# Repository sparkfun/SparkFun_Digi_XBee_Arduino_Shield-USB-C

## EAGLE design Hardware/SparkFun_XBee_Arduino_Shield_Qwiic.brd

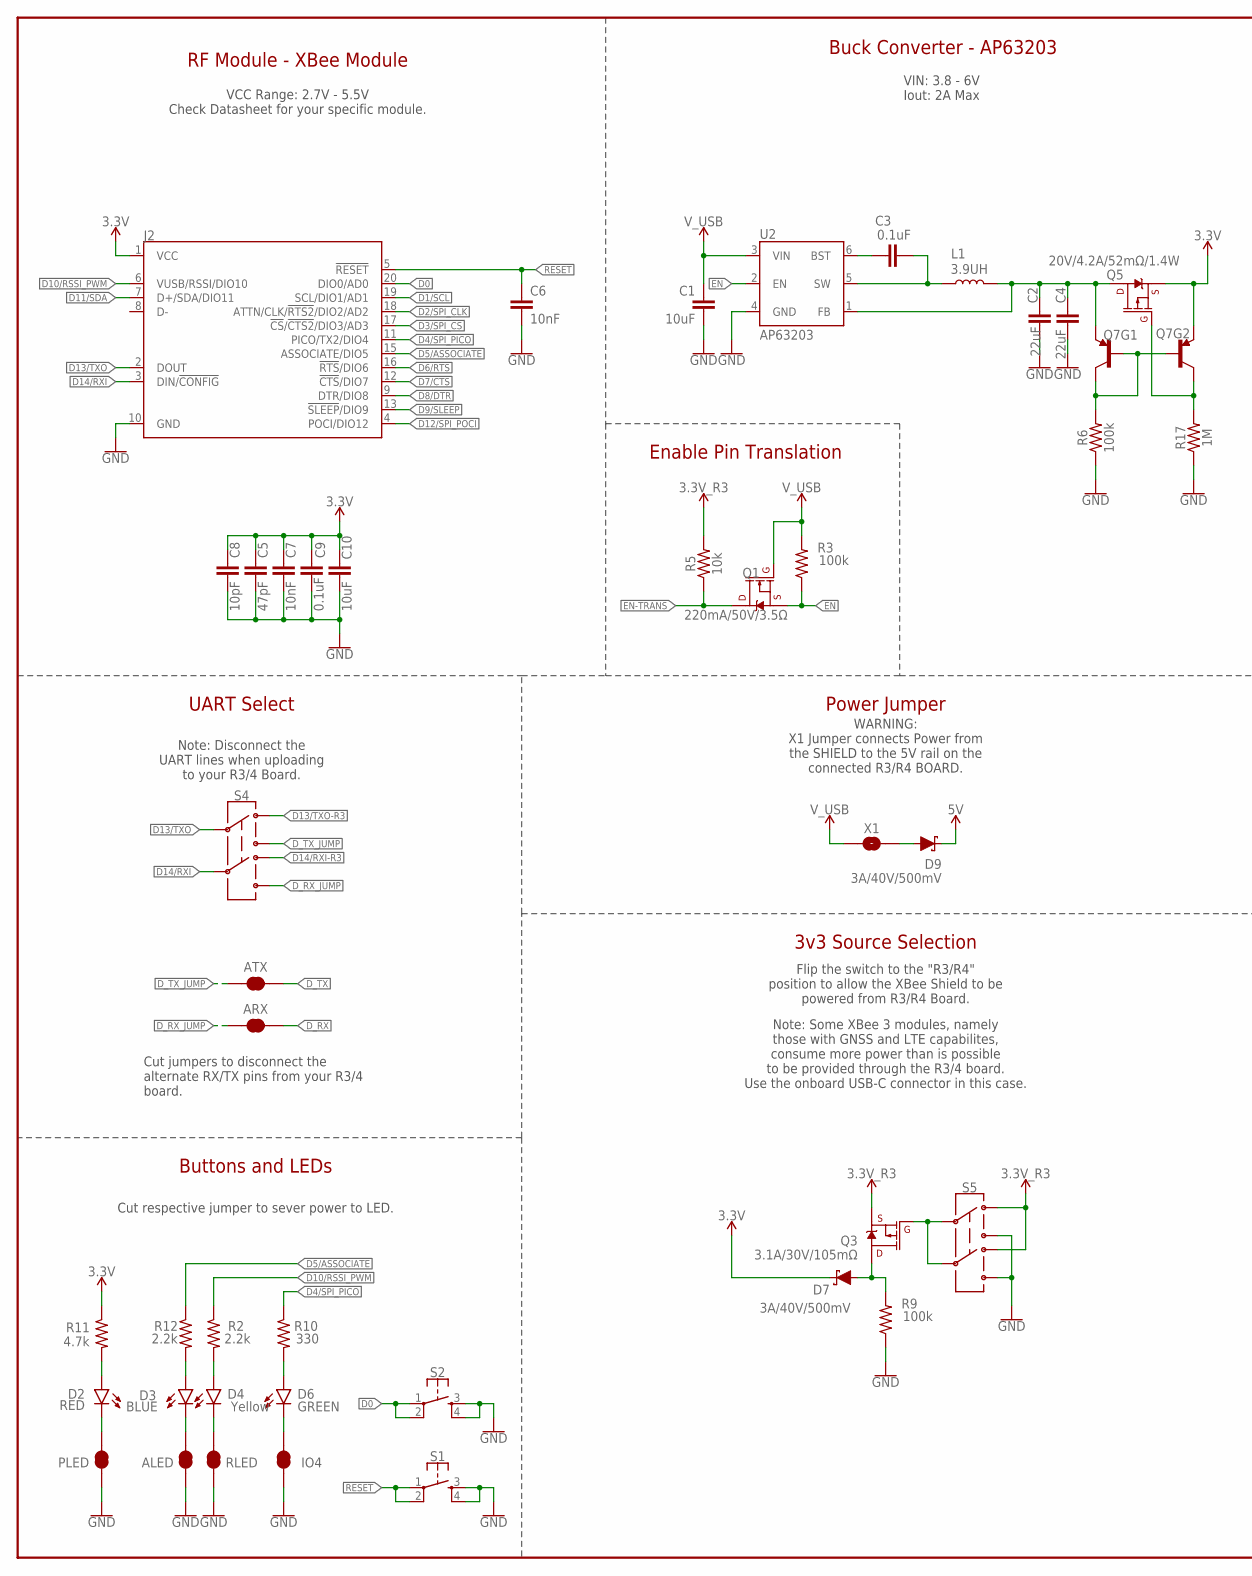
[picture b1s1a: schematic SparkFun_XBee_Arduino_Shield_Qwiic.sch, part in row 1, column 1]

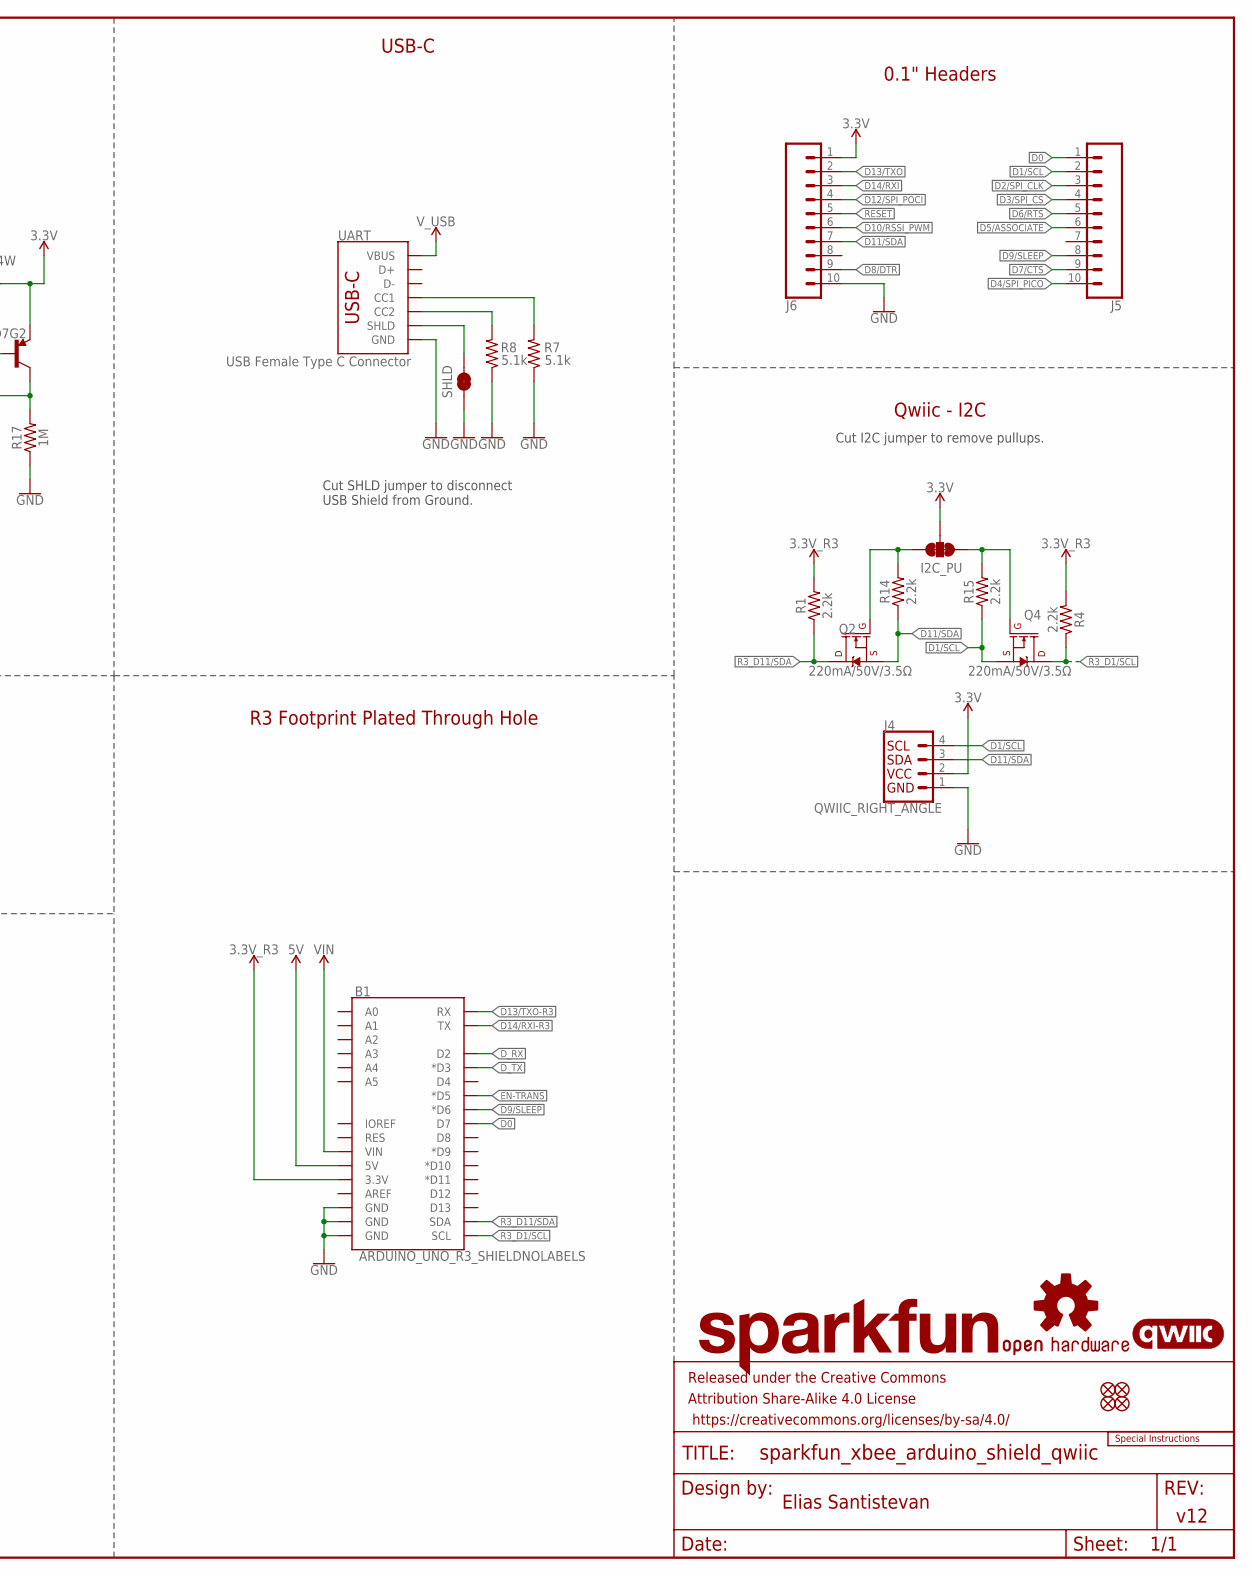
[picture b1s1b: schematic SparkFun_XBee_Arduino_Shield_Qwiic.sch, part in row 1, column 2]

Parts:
ALED: JUMPER-SMT_2_NC_TRACE_SILK; SMT-JUMPER_2_NC_TRACE_SILK
ARX: JUMPER-SMT_2_NC_TRACE_SILK; SMT-JUMPER_2_NC_TRACE_SILK
ATX: JUMPER-SMT_2_NC_TRACE_SILK; SMT-JUMPER_2_NC_TRACE_SILK
B1: ARDUINO_UNO_R3_SHIELDNOLABELS; UNO_R3_SHIELD_NOLABELS
C1: 10uF; 1210
C2, C4: 22uF; 0603
C3, C9: 0.1uF; 0603
C5: 47pF; 0603
C6, C7: 10nF; 0603
C8: 10pF; 0603
C10: 10uF; 0603
D2: RED; LED-0603
D3: BLUE; LED-0603
D4: Yellow; LED-0603
D6: GREEN; LED-0603
D7, D9: 3A/40V/500mV; SMA-DIODE
FD1, FD2, FD3, FD4: FIDUCIAL1X2; FIDUCIAL-1X2
FRAME1: FRAME-LEDGER; CREATIVE_COMMONS
I2C_PU: JUMPER-SMT_3_2-NC_TRACE_SILK; SMT-JUMPER_3_2-NC_TRACE_SILK
IO4: JUMPER-SMT_2_NC_TRACE_SILK; SMT-JUMPER_2_NC_TRACE_SILK
J2: XBEE_UPDATEXBEE_SMD; XBEE3-SMD
J4: QWIIC_RIGHT_ANGLE; JST04_1MM_RA
J5, J6: CONN_10NO_SILK_PTH_FEMALE; 1X10_NO_SILK
L1: 3.9UH; INDUCTOR_3.9UH
LOGO1: SFE_LOGO_NAMEBLANK; BLANK
LOGO2: OSHW-LOGOS; OSHW-LOGO-S
LOGO3: QWIIC_LOGO_4MM; QWIIC_4MM
LOGO4: SPECIAL_INSTRUCTIONS-ORDERING; ORDERING_INSTRUCTIONS
PLED: JUMPER-SMT_2_NC_TRACE_SILK; SMT-JUMPER_2_NC_TRACE_SILK
Q1, Q2, Q4: 220mA/50V/3.5Ω; SOT23-3
Q3: 3.1A/30V/105mΩ; SOT23-3
Q5: 20V/4.2A/52mΩ/1.4W; SOT23-3
Q7: TRANS_PNP_DUALSOT-363; SOT363_PHILIPS
R1, R2, R4, R12, R14, R15: 2.2k; 0603
R3, R6, R9: 100k; 0603
R5: 10k; 0603
R7, R8: 5.1k; 0603
R10: 330; 0603
R11: 4.7k; 0603
R17: 1M; 0603
RLED: JUMPER-SMT_2_NC_TRACE_SILK; SMT-JUMPER_2_NC_TRACE_SILK
S1, S2: MOMENTARY-SWITCH-SPST-2-SMD-5.2MM-TALL; TACTILE_SWITCH_SMD_5.2MM
S4, S5: SWITCH-DPDT-SMD-AYZ0202; SWITCH_DPDT_SMD_AYZ0202
SHLD: JUMPER-SMT_2_NC_TRACE_SILK; SMT-JUMPER_2_NC_TRACE_SILK
U2: AP63203; SOT23-6
UART: USB Female Type C Connector; USB-C-16P-4LAYER-ISOLATED
X1: JUMPER-SMT_2_NO_SILK; SMT-JUMPER_2_NO_SILK

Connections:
3.3V: C5.1, C7.1, C8.1, C9.1, C10.1, D7.C, I2C_PU.2, J2.1 (VCC), J4.2, J6.1, Q5.2 (S), Q7.4 (E), R11.1
3.3V_R3: B1.3.3V, Q3.2 (S), R1.2, R4.2, R5.2, S5.3, S5.6
3.3V_VREG: C2.1, C4.1, L1.P$2 (2), Q5.3 (D), Q7.1 (E), U2.1 (FB)
5V: B1.5V, D9.C
!RESET!: C6.1, J2.5 (!RESET!), J6.5, S1.1, S1.2
D0: B1.D7, J2.20 (DIO0/AD0), J5.1, S2.1, S2.2
D1/SCL: J2.19 (SCL/DIO1/AD1), J4.4, J5.2, Q4.2 (S), R15.1
D2/SPI_CLK: J2.18 (ATTN/CLK/!RTS2!/DIO2/AD2), J5.3
D3/SPI_!CS!: J2.17 (!CS!/!CTS2!/DIO3/AD3), J5.4
D4/SPI_PICO: J2.11 (PICO/TX2/DIO4), J5.10, R10.1
D5/ASSOCIATE: J2.15 (ASSOCIATE/DIO5), J5.6, R12.1
D6/!RTS!: J2.16 (!RTS!/DIO6), J5.5
D7/!CTS!: J2.12 (!CTS!/DIO7), J5.9
D8/!DTR!: J2.9 (DTR/DIO8), J6.9
D9/!SLEEP!: B1.D6 (*D6), J2.13 (!SLEEP!/DIO9), J5.8
D10/RSSI_PWM: J2.6 (VUSB/RSSI/DIO10), J6.6, R2.1
D11/SDA: J2.7 (D+/SDA/DIO11), J4.3, J6.7, Q2.2 (S), R14.1
D12/SPI_POCI: J2.4 (POCI/DIO12), J6.4
D13/TXO: J2.2 (DOUT), J6.2, S4.2
D13/TXO-R3: B1.RX, S4.3
D14/RXI: J2.3 (DIN/!CONFIG!), J6.3, S4.5
D14/RXI-R3: B1.TX, S4.6
D_RX: ARX.2, B1.D2
D_RX_JUMP: ARX.1, S4.4
D_TX: ATX.2, B1.D3 (*D3)
D_TX_JUMP: ATX.1, S4.1
EN: Q1.2 (S), R3.1, U2.2 (EN)
EN-TRANS: B1.D5 (*D5), Q1.3 (D), R5.1
GND: ALED.1, B1.GND@0 (GND), B1.GND@1 (GND), B1.GND@2 (GND), C1.2, C2.2, C4.2, C5.2, C6.2, C7.2, C8.2, C9.2, C10.2, IO4.1, J2.10 (GND), J4.1, J6.10, PLED.1, R6.1, R7.1, R8.1, R9.1, R17.1, RLED.1, S1.3, S1.4, S2.3, S2.4, S5.1, S5.4, SHLD.1, U2.4 (GND), UART.GND, UART.GND2 (GND)
unnamed: C3.1, U2.6 (BST)
unnamed: D4.A, R2.2
unnamed: D4.C, RLED.2
unnamed: D6.A, R10.2
unnamed: R8.2, UART.B5 (CC2)
unnamed: R7.2, UART.A5 (CC1)
unnamed: D2.A, R11.2
unnamed: C3.2, L1.P$1 (1), U2.5 (SW)
unnamed: D9.A, X1.2
unnamed: I2C_PU.1, Q4.1 (G), R15.2
unnamed: I2C_PU.3, Q2.1 (G), R14.2
unnamed: D3.A, R12.2
unnamed: D7.A, Q3.3 (D), R9.2
unnamed: D6.C, IO4.2
unnamed: Q7.2 (B), Q7.5 (B), Q7.6 (C), R6.2
unnamed: Q5.1 (G), Q7.3 (C), R17.2
unnamed: ALED.2, D3.C
unnamed: D2.C, PLED.2
unnamed: Q3.1 (G), S5.2, S5.5
R3_D1/SCL: B1.SCL, Q4.3 (D), R4.1
R3_D11/SDA: B1.SDA, Q2.3 (D), R1.1
SHLD: SHLD.2, UART.SHLD1 (SHLD), UART.SHLD2 (SHLD), UART.SHLD3 (SHLD), UART.SHLD4 (SHLD), UART.SHLD5 (SHLD), UART.SHLD6 (SHLD), UART.SHLD7 (SHLD), UART.SHLD8 (SHLD)
VIN: B1.VIN
V_USB: C1.1, Q1.1 (G), R3.2, U2.3 (VIN), UART.VBUS1 (VBUS), UART.VBUS2 (VBUS), X1.1

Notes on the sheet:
VCC Range: 2.7V - 5.5V Check Datasheet for your specific module.
Buck Converter - AP63203
Qwiic - I2C
v12
Elias Santistevan
Buttons and LEDs
VIN: 3.8 - 6V Iout: 2A Max
Cut I2C jumper to remove pullups.
Cut respective jumper to sever power to LED.
RF Module - XBee Module
0.1" Headers
Cut SHLD jumper to disconnect USB Shield from Ground.
USB-C
R3 Footprint Plated Through Hole
Power Jumper
Enable Pin Translation
3v3 Source Selection
WARNING: X1 Jumper connects Power from the SHIELD to the 5V rail on the connected R3/R4 BOARD.
Flip the switch to the "R3/R4" position to allow the XBee Shield to be powered from R3/R4 Board.
Note: Some XBee 3 modules, namely those with GNSS and LTE capabilites, consume more power than is possible to be provided through the R3/4 board. Use the onboard USB-C connector in this case.
UART Select
Note: Disconnect the UART lines when uploading to your R3/4 Board.
Cut jumpers to disconnect the alternate RX/TX pins from your R3/4 board.

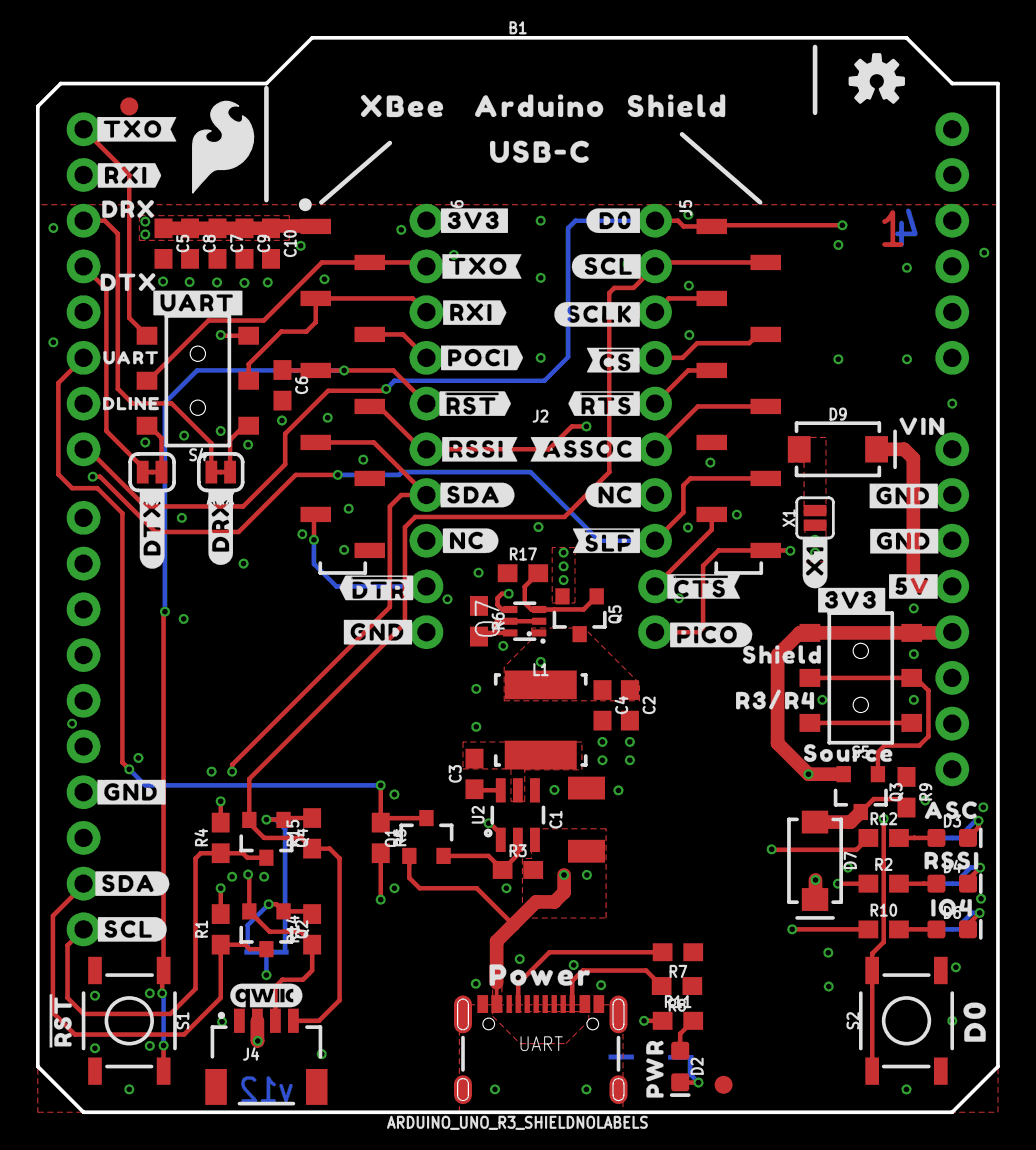
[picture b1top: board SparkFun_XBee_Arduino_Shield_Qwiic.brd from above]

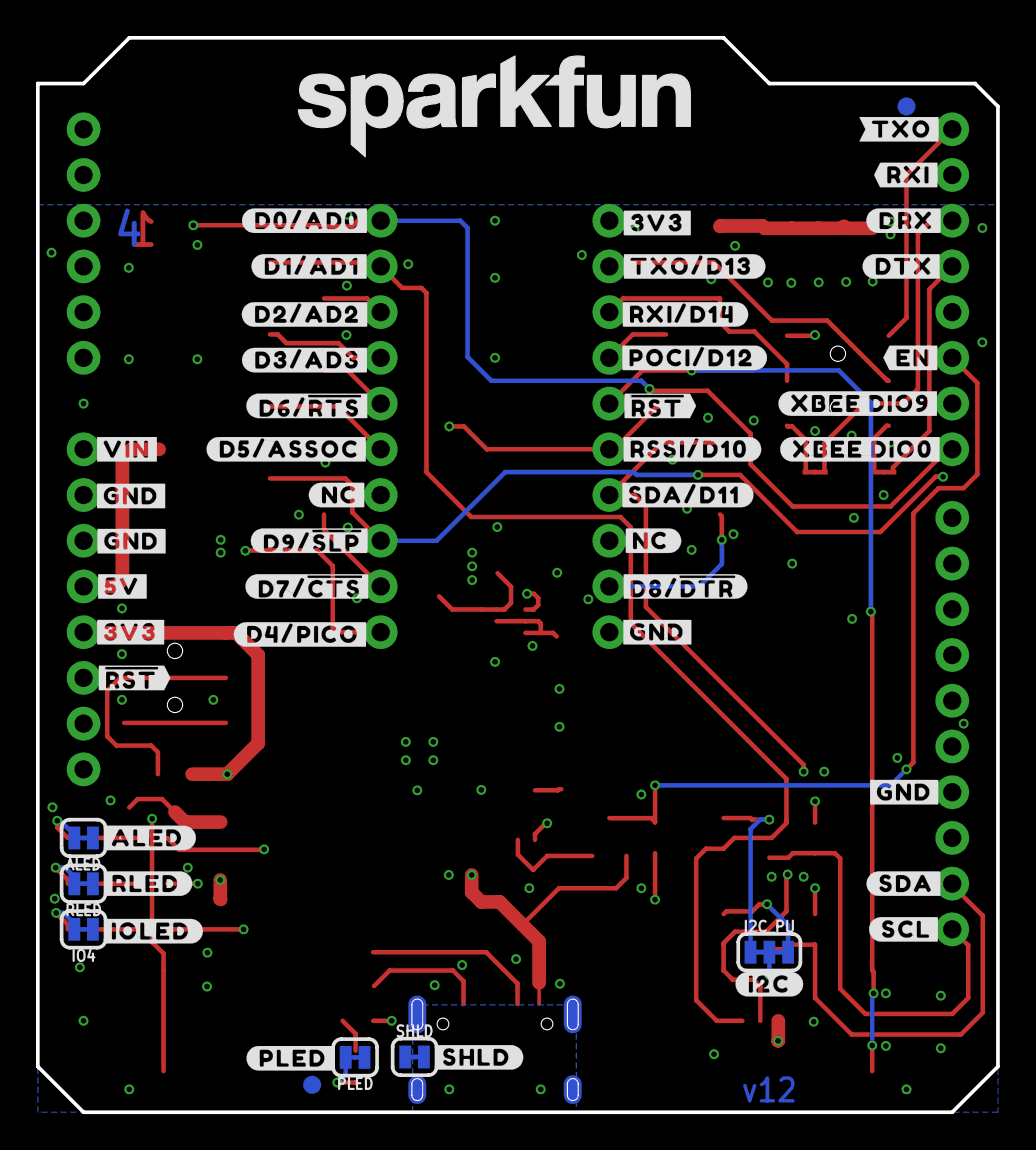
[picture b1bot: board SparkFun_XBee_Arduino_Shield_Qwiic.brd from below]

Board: 4 copper layers, 53.3 x 59.7 mm, 163 parts (51 on the bottom side), 52 nets.

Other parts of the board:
U$1: RSSI31
U$2: PWR29
U$3, U$56: #SDA#10
U$4: #SHLD#36
U$5, U$9: #NC#1
U$6: #D3#AD3#23
U$7, U$10: #NC#3
U$8: ##DTR##27
U$11: #D1#AD1#8
U$12: ##CTS##28
U$13: #D8##DTR##27
U$14: #RSSI#D10#17
U$15: #SDA#D11#9
U$16: ##RST##15
U$17: #POCI#D12#24
U$18: #RXI#D14#15
U$19: #D2#AD2#19
U$20: #D6##RTS##25
U$21, U$32: #TXO#8
U$22: #TXO#D13#13
U$23: VIN5
U$24: #SCL#7
U$25, U$29, U$41, U$50, U$53, U$63, U$76, U$82: #GND#0
U$26: #I2C#33
U$27, U$33: #RXI#7
U$28: DRX52
U$30: #RST#30
U$31: #PICO#27
U$34: DTX53
U$35: #D5#ASSOC#25
U$36: #D9##SLP##28
U$37: #D7##CTS##26
U$38: #D4#PICO#25
U$39, U$66: #5V#5
U$40: D03
U$42: DLINE45
U$43: #X1#10
U$44, U$47, U$77, U$84: #3V3#1
U$45: #POCI#32
U$46: SHIELD55
U$48: UART44
U$49: #ALED#21
U$51: #RLED#22
U$52: #PLED#20
U$54, U$87: ##RST##13
U$55: #RSSI#16
U$57: #ASSOC#28
U$58: ##RTS##14
U$59: ##CS##26
U$60: #SCLK#33
U$61: SFE_LOGO_FLAME_.2
U$62: SFE_LOGO_NAME_.2
U$64: #SCL#9
U$65: #D0#3
U$67: #SDA#9
U$68: ##SLP##28
U$69: R3#R455
U$70: #SCL#13
U$71, U$86: #DRX#56
U$72, U$89: #DTX#57
U$73: #TXO#61
U$74: ASC32
U$75: POWER49
U$78: #D0#AD0#18
U$79: ARDUINO1345
U$80: XBEE340
U$81: SHIELD1346
U$83: #EN#15
U$85: #RXI#60
U$88: #VIN#4
U$90: #XBEE_DIO0#62
U$91: #UART#4048234
U$92: #XBEE_DIO9#62
U$93: #IOLED#5
U$94: IO49
U$95: SOURCE54
U$96: USB#C58

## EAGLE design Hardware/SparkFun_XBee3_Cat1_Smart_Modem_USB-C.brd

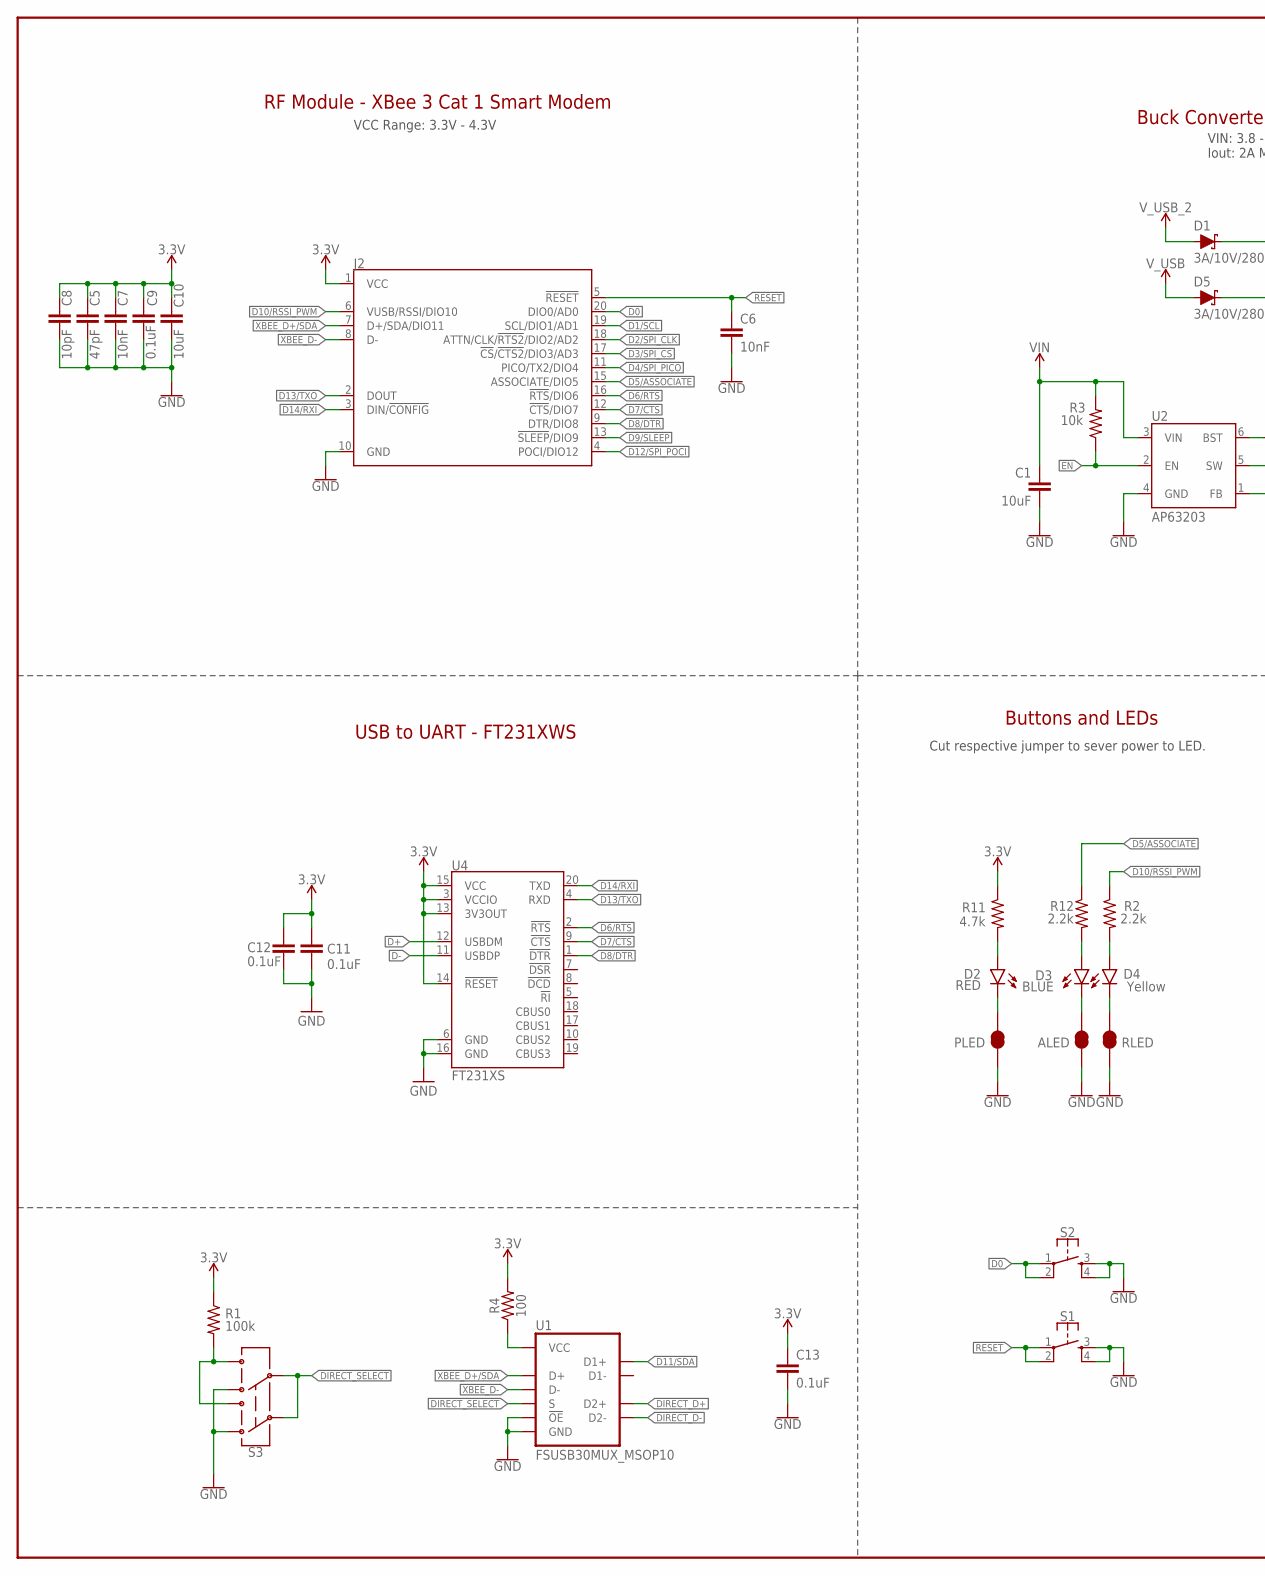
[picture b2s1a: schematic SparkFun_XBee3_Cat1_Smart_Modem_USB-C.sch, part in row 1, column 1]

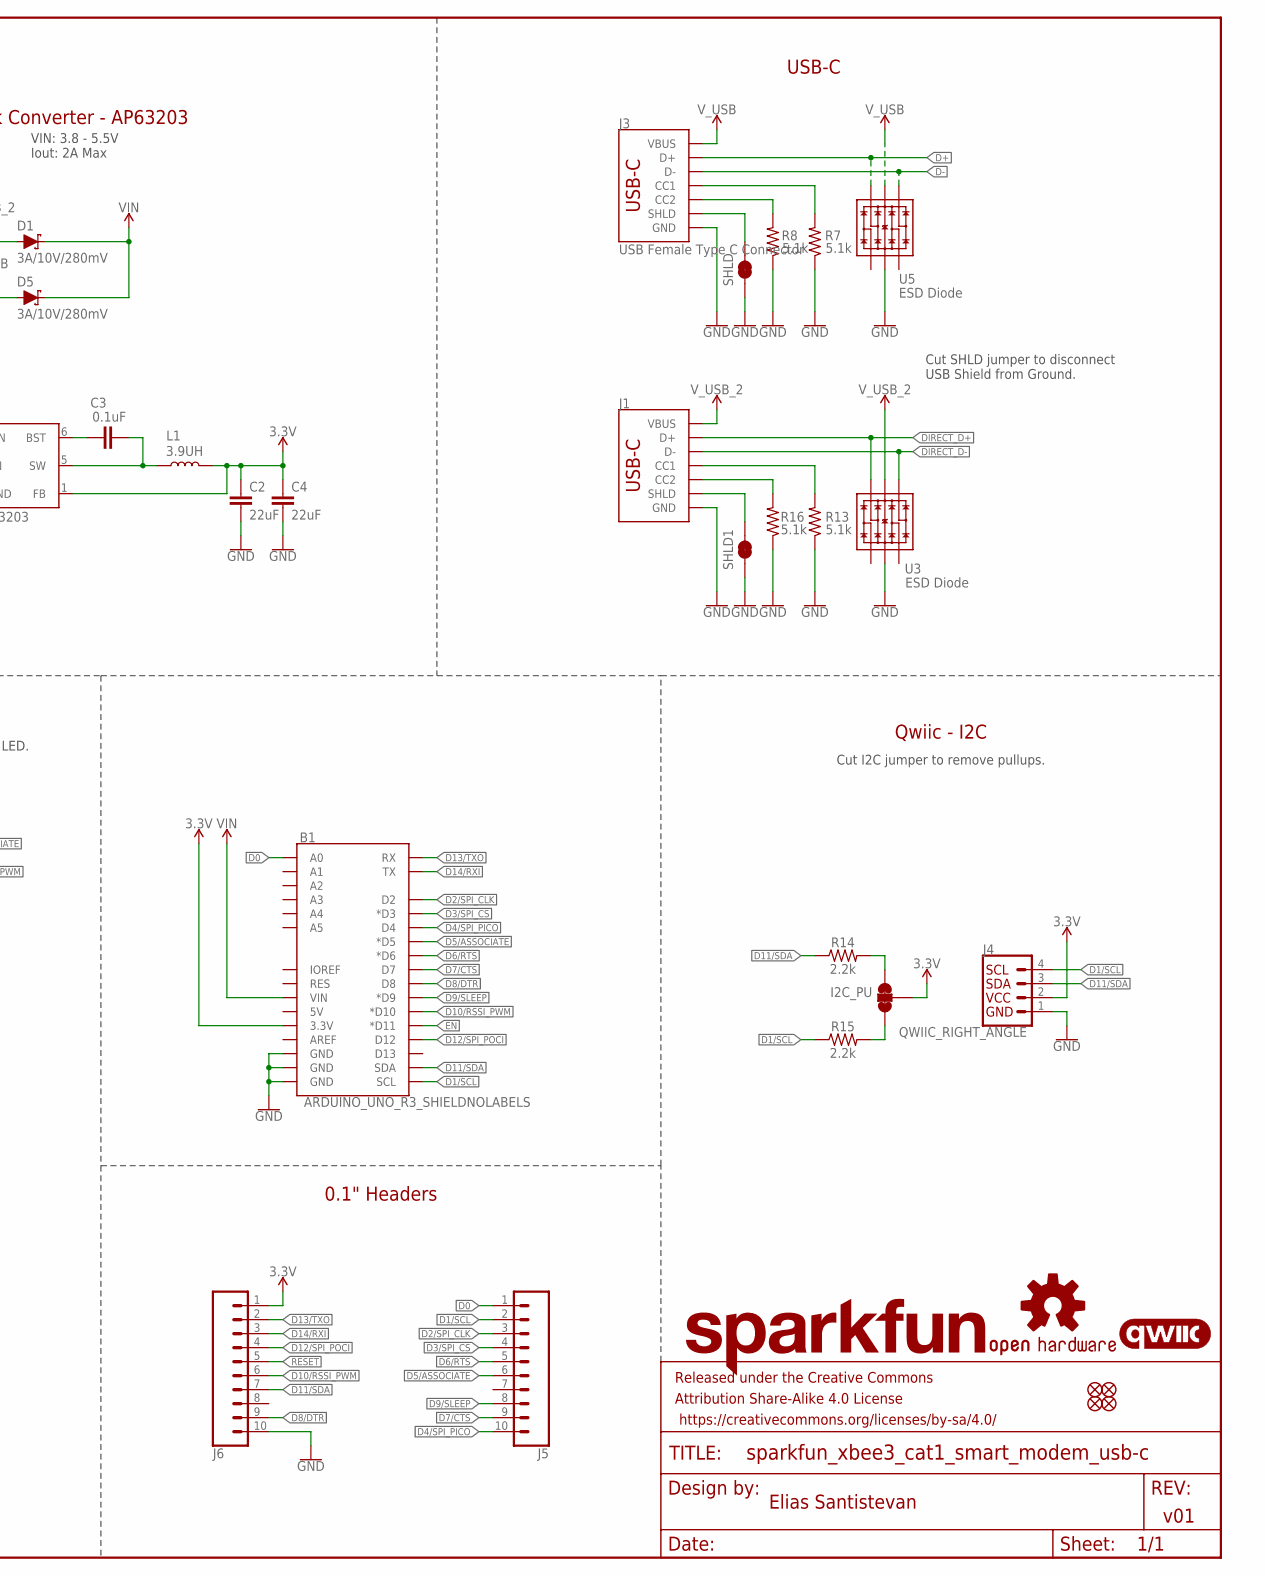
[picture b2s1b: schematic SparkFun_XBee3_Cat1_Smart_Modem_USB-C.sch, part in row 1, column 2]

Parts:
ALED: JUMPER-SMT_2_NC_TRACE_SILK; SMT-JUMPER_2_NC_TRACE_SILK
B1: ARDUINO_UNO_R3_SHIELDNOLABELS; UNO_R3_SHIELD_NOLABELS
C1: 10uF; 1210
C2, C4: 22uF; 0603
C3, C9, C11, C12, C13: 0.1uF; 0603
C5: 47pF; 0603
C6, C7: 10nF; 0603
C8: 10pF; 0603
C10: 10uF; 0603
D1, D5: 3A/10V/280mV; SOD-323
D2: RED; LED-0603
D3: BLUE; LED-0603
D4: Yellow; LED-0603
FD1, FD2, FD3, FD4: FIDUCIAL1X2; FIDUCIAL-1X2
FRAME1: FRAME-LEDGER; CREATIVE_COMMONS
I2C_PU: JUMPER-SMT_3_2-NC_TRACE_SILK; SMT-JUMPER_3_2-NC_TRACE_SILK
J1, J3: USB Female Type C Connector; USB-C-16P-4LAYER-ISOLATED
J2: XBEE_UPDATEXBEE_SMD_SILK; XBEE3-SMD_SILK
J4: QWIIC_RIGHT_ANGLE; JST04_1MM_RA
J5, J6: CONN_10NO_SILK_PTH_FEMALE; 1X10_NO_SILK
L1: 3.9UH; INDUCTOR_3.9UH
LOGO1: SFE_LOGO_NAME.1_INCH; SFE_LOGO_NAME_.1
LOGO2: OSHW-LOGOS; OSHW-LOGO-S
LOGO3: QWIIC_LOGO_3MM; QWIIC_3MM
PLED: JUMPER-SMT_2_NC_TRACE_SILK; SMT-JUMPER_2_NC_TRACE_SILK
R1: 100k; 0603
R2, R12, R14, R15: 2.2k; 0603
R3: 10k; 0603
R4: 100; 0603
R7, R8, R13, R16: 5.1k; 0603
R11: 4.7k; 0603
RLED: JUMPER-SMT_2_NC_TRACE_SILK; SMT-JUMPER_2_NC_TRACE_SILK
S1, S2: MOMENTARY-SWITCH-SPST-2-SMD-5.2MM-TALL; TACTILE_SWITCH_SMD_5.2MM
S3: SWITCH-DPDT-SMD-AYZ0202; SWITCH_DPDT_SMD_AYZ0202
SHLD, SHLD1: JUMPER-SMT_2_NC_TRACE_SILK; SMT-JUMPER_2_NC_TRACE_SILK
U1: FSUSB30MUX_MSOP10; MSOP10
U2: AP63203; SOT23-6
U3, U5: ESD Diode; SOT-23-6
U4: FT231XS; SSOP20_L

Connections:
3.3V: B1.3.3V, C2.1, C4.1, C5.1, C7.1, C8.1, C9.1, C10.1, C11.1, C12.1, C13.1, I2C_PU.2, J2.1 (VCC), J4.2, J6.1, L1.P$2 (2), R1.1, R4.2, R11.1, U2.1 (FB), U4.3 (VCCIO), U4.13 (3V3OUT), U4.14 (!RESET), U4.15 (VCC)
!RESET!: C6.1, J2.5 (!RESET!), J6.5, S1.1, S1.2
D0: B1.A0, J2.20 (DIO0/AD0), J5.1, S2.1, S2.2
D1/SCL: B1.SCL, J2.19 (SCL/DIO1/AD1), J4.4, J5.2, R15.1
D2/SPI_CLK: B1.D2, J2.18 (ATTN/CLK/!RTS2!/DIO2/AD2), J5.3
D3/SPI_!CS!: B1.D3 (*D3), J2.17 (!CS!/!CTS2!/DIO3/AD3), J5.4
D4/SPI_PICO: B1.D4, J2.11 (PICO/TX2/DIO4), J5.10
D5/ASSOCIATE: B1.D5 (*D5), J2.15 (ASSOCIATE/DIO5), J5.6, R12.1
D6/!RTS!: B1.D6 (*D6), J2.16 (!RTS!/DIO6), J5.5, U4.2 (!RTS)
D7/!CTS!: B1.D7, J2.12 (!CTS!/DIO7), J5.9, U4.9 (!CTS)
D8/!DTR!: B1.D8, J2.9 (DTR/DIO8), J6.9, U4.1 (!DTR)
D9/!SLEEP!: B1.D9 (*D9), J2.13 (!SLEEP!/DIO9), J5.8
D10/RSSI_PWM: B1.D10 (*D10), J2.6 (VUSB/RSSI/DIO10), J6.6, R2.1
D11/SDA: B1.SDA, J4.3, J6.7, R14.1, U1.2 (D1+)
D12/SPI_POCI: B1.D12, J2.4 (POCI/DIO12), J6.4
D13/TXO: B1.RX, J2.2 (DOUT), J6.2, U4.4 (RXD)
D14/RXI: B1.TX, J2.3 (DIN/!CONFIG!), J6.3, U4.20 (TXD)
D+: J3.A6 (D+), J3.B6 (D+), U4.12 (USBDM), U5.6 (IO4)
D-: J3.A7 (D-), J3.B7 (D-), U4.11 (USBDP), U5.4 (IO3)
DIRECT_D+: J1.A6 (D+), J1.B6 (D+), U1.3 (D2+), U3.6 (IO4)
DIRECT_D-: J1.A7 (D-), J1.B7 (D-), U1.7 (D2-), U3.4 (IO3)
DIRECT_SELECT: S3.2, S3.5, U1.1 (S)
EN: B1.D11 (*D11), R3.1, U2.2 (EN)
FIRMWARE: R1.2, S3.1, S3.4
GND: ALED.1, B1.GND@0 (GND), B1.GND@1 (GND), B1.GND@2 (GND), C1.2, C2.2, C4.2, C5.2, C6.2, C7.2, C8.2, C9.2, C10.2, C11.2, C12.2, C13.2, J1.GND, J1.GND2 (GND), J2.10 (GND), J3.GND, J3.GND2 (GND), J4.1, J6.10, PLED.1, R7.1, R8.1, R13.1, R16.1, RLED.1, S1.3, S1.4, S2.3, S2.4, S3.3, S3.6, SHLD.1, SHLD1.1, U1.5 (GND), U1.9 (!OE!), U2.4 (GND), U3.2 (VSS), U4.6 (GND), U4.16 (GND), U5.2 (VSS)
unnamed: C3.1, U2.6 (BST)
unnamed: D4.A, R2.2
unnamed: D4.C, RLED.2
unnamed: J3.B5 (CC2), R8.2
unnamed: J3.A5 (CC1), R7.2
unnamed: D2.A, R11.2
unnamed: C3.2, L1.P$1 (1), U2.5 (SW)
unnamed: R4.1, U1.10 (VCC)
unnamed: I2C_PU.3, R14.2
unnamed: D3.A, R12.2
unnamed: I2C_PU.1, R15.2
unnamed: J1.B5 (CC2), R16.2
unnamed: J1.A5 (CC1), R13.2
unnamed: ALED.2, D3.C
unnamed: D2.C, PLED.2
SHLD: J3.SHLD1 (SHLD), J3.SHLD2 (SHLD), J3.SHLD3 (SHLD), J3.SHLD4 (SHLD), J3.SHLD5 (SHLD), J3.SHLD6 (SHLD), J3.SHLD7 (SHLD), J3.SHLD8 (SHLD), SHLD.2
SHLD1: J1.SHLD1 (SHLD), J1.SHLD2 (SHLD), J1.SHLD3 (SHLD), J1.SHLD4 (SHLD), J1.SHLD5 (SHLD), J1.SHLD6 (SHLD), J1.SHLD7 (SHLD), J1.SHLD8 (SHLD), SHLD1.2
VIN: B1.VIN, C1.1, D1.C, D5.C, R3.2, U2.3 (VIN)
V_USB: D5.A, J3.VBUS1 (VBUS), J3.VBUS2 (VBUS), U5.5 (VCC)
V_USB_2: D1.A, J1.VBUS1 (VBUS), J1.VBUS2 (VBUS), U3.5 (VCC)
XBEE_D+/SDA: J2.7 (D+/SDA/DIO11), U1.4 (D+)
XBEE_D-: J2.8 (D-), U1.6 (D-)

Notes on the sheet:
VCC Range: 3.3V - 4.3V
Buck Converter - AP63203
Qwiic - I2C
v01
Elias Santistevan
Buttons and LEDs
VIN: 3.8 - 5.5V Iout: 2A Max
Cut I2C jumper to remove pullups.
Cut respective jumper to sever power to LED.
RF Module - XBee 3 Cat 1 Smart Modem
0.1" Headers
Cut SHLD jumper to disconnect USB Shield from Ground.
USB to UART - FT231XWS
USB-C

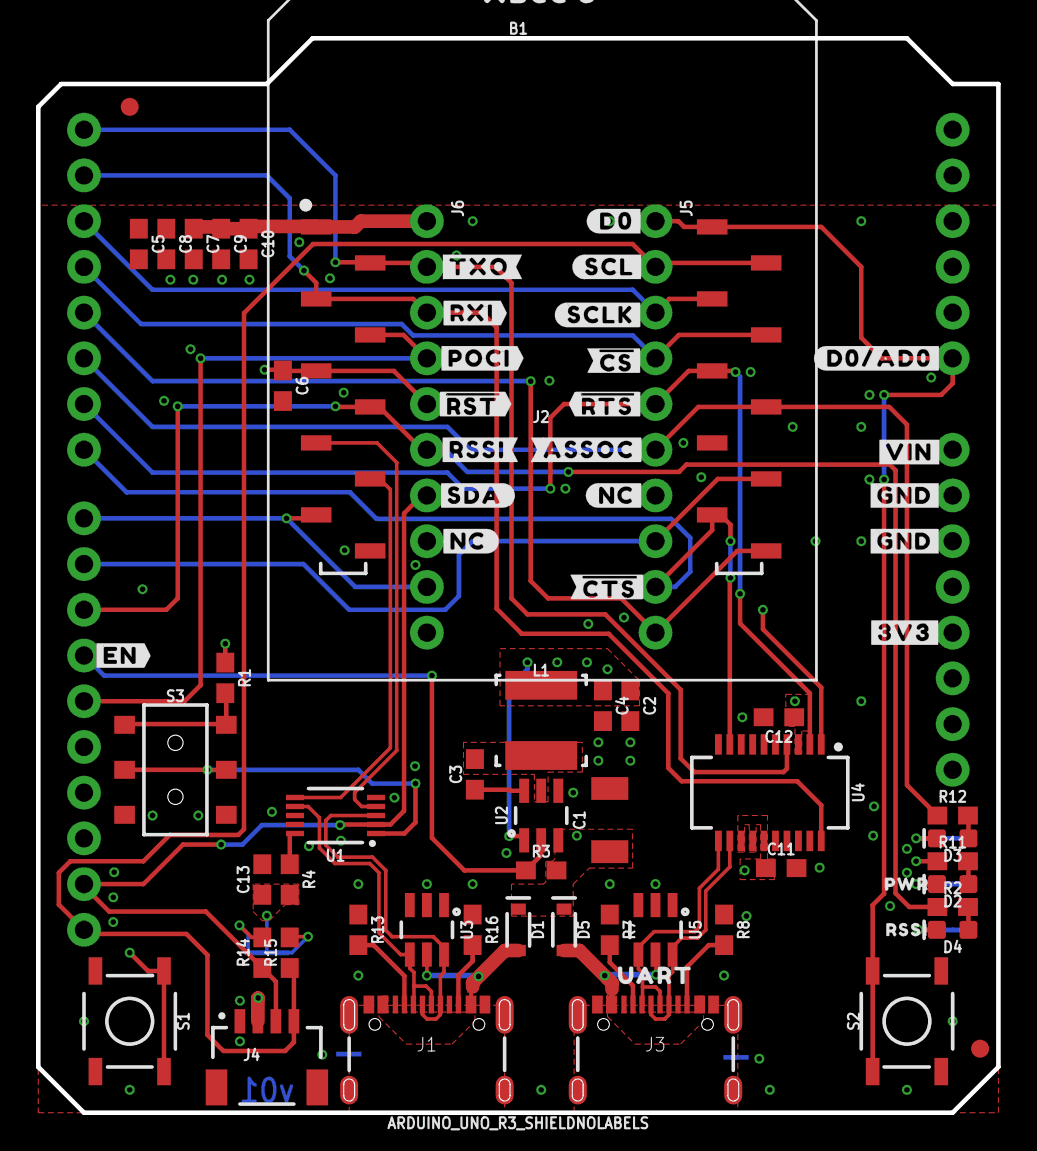
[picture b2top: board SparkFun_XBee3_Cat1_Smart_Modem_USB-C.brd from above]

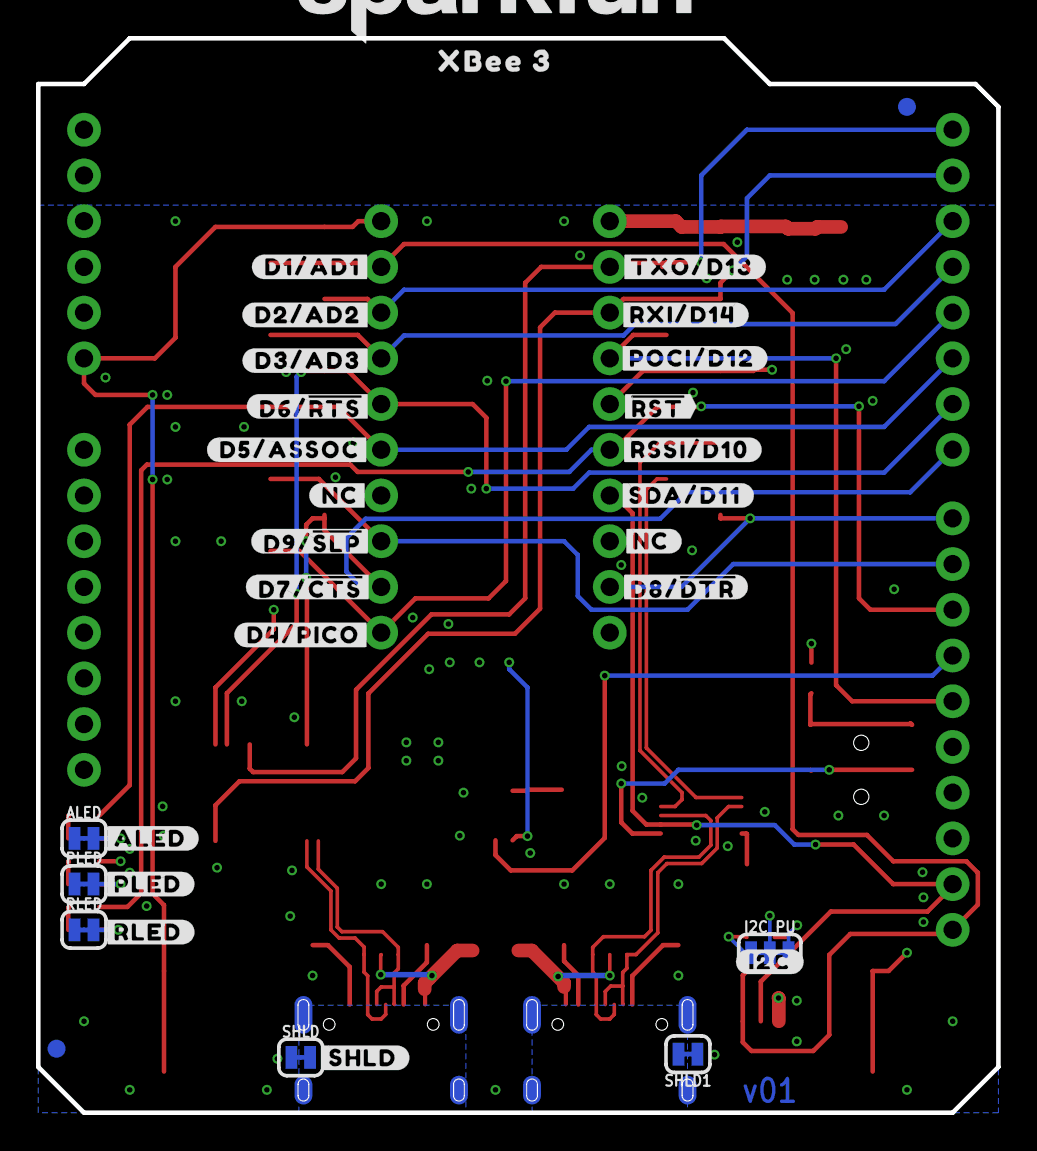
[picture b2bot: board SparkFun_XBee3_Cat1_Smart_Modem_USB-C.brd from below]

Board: 4 copper layers, 53.3 x 59.7 mm, 112 parts (32 on the bottom side), 47 nets.

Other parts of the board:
U$1: RSSI31
U$2: PWR29
U$4: #SHLD#36
U$5, U$9: #NC#1
U$6: #D3#AD3#23
U$7, U$10: #NC#3
U$8: #D0#AD0#18
U$11: #D1#AD1#8
U$12, U$29: #GND#0
U$13: #D8##DTR##27
U$14: #RSSI#D10#17
U$15: #SDA#D11#9
U$16: ##RST##15
U$17: #POCI#D12#24
U$18: #RXI#D14#15
U$19: #D2#AD2#19
U$20: #D6##RTS##25
U$21: #TXO#8
U$22: #TXO#D13#13
U$23, U$53: XBEE_335
U$26: #I2C#33
U$27: #RXI#7
U$28: UART34
U$30: #RST#30
U$31: ##CTS##26
U$35: #D5#ASSOC#25
U$36: #D9##SLP##28
U$37: #D7##CTS##26
U$38: #D4#PICO#25
U$40: D03
U$44: #3V3#1
U$45: #POCI#32
U$48: #EN#17
U$49: #ALED#21
U$51: #RLED#22
U$52: #PLED#20
U$54: ##RST##13
U$55: #RSSI#16
U$56: #SDA#10
U$57: #ASSOC#28
U$58: ##RTS##14
U$59: ##CS##26
U$60: #SCLK#33
U$61: SFE_LOGO_FLAME_.2
U$63: SFE_LOGO_NAME_.2
U$64: #SCL#9
U$65: #D0#3
U$66: #VIN#4

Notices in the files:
parts and their libraries:
SparkFun-Capacitors: Licensing: Creative Commons ShareAlike 4.0 International - https://creativecommons.org/licenses/by-sa/4.0
SparkFun-Aesthetics: Released under the Creative Commons Attribution Share-Alike 4.0 License
SparkFun-Aesthetics: https://creativecommons.org/licenses/by-sa/4.0
